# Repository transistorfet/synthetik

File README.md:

Synthetik
=========

###### *Started October 21, 2020*

This project started after I bought some old sound synthesis chips that were commonly used in
video game consoles and computers from the 80s and early 90s.  The first revision is a shield
for an Arduino Mega with 4 different chips: the General Instruments AY-3-8910 / Yamaha YM2149,
the YM2612 / YM3438 (OPN), the YM3812 (OPL2), and the YMF262 (OPL3).  It also has a MIDI in
port, line out stereo jack, and a headphone stereo jack with a TDA1308 power amplifier.

The board design had a large number of issues and mistakes, and I've so far only got it working
with one chip.

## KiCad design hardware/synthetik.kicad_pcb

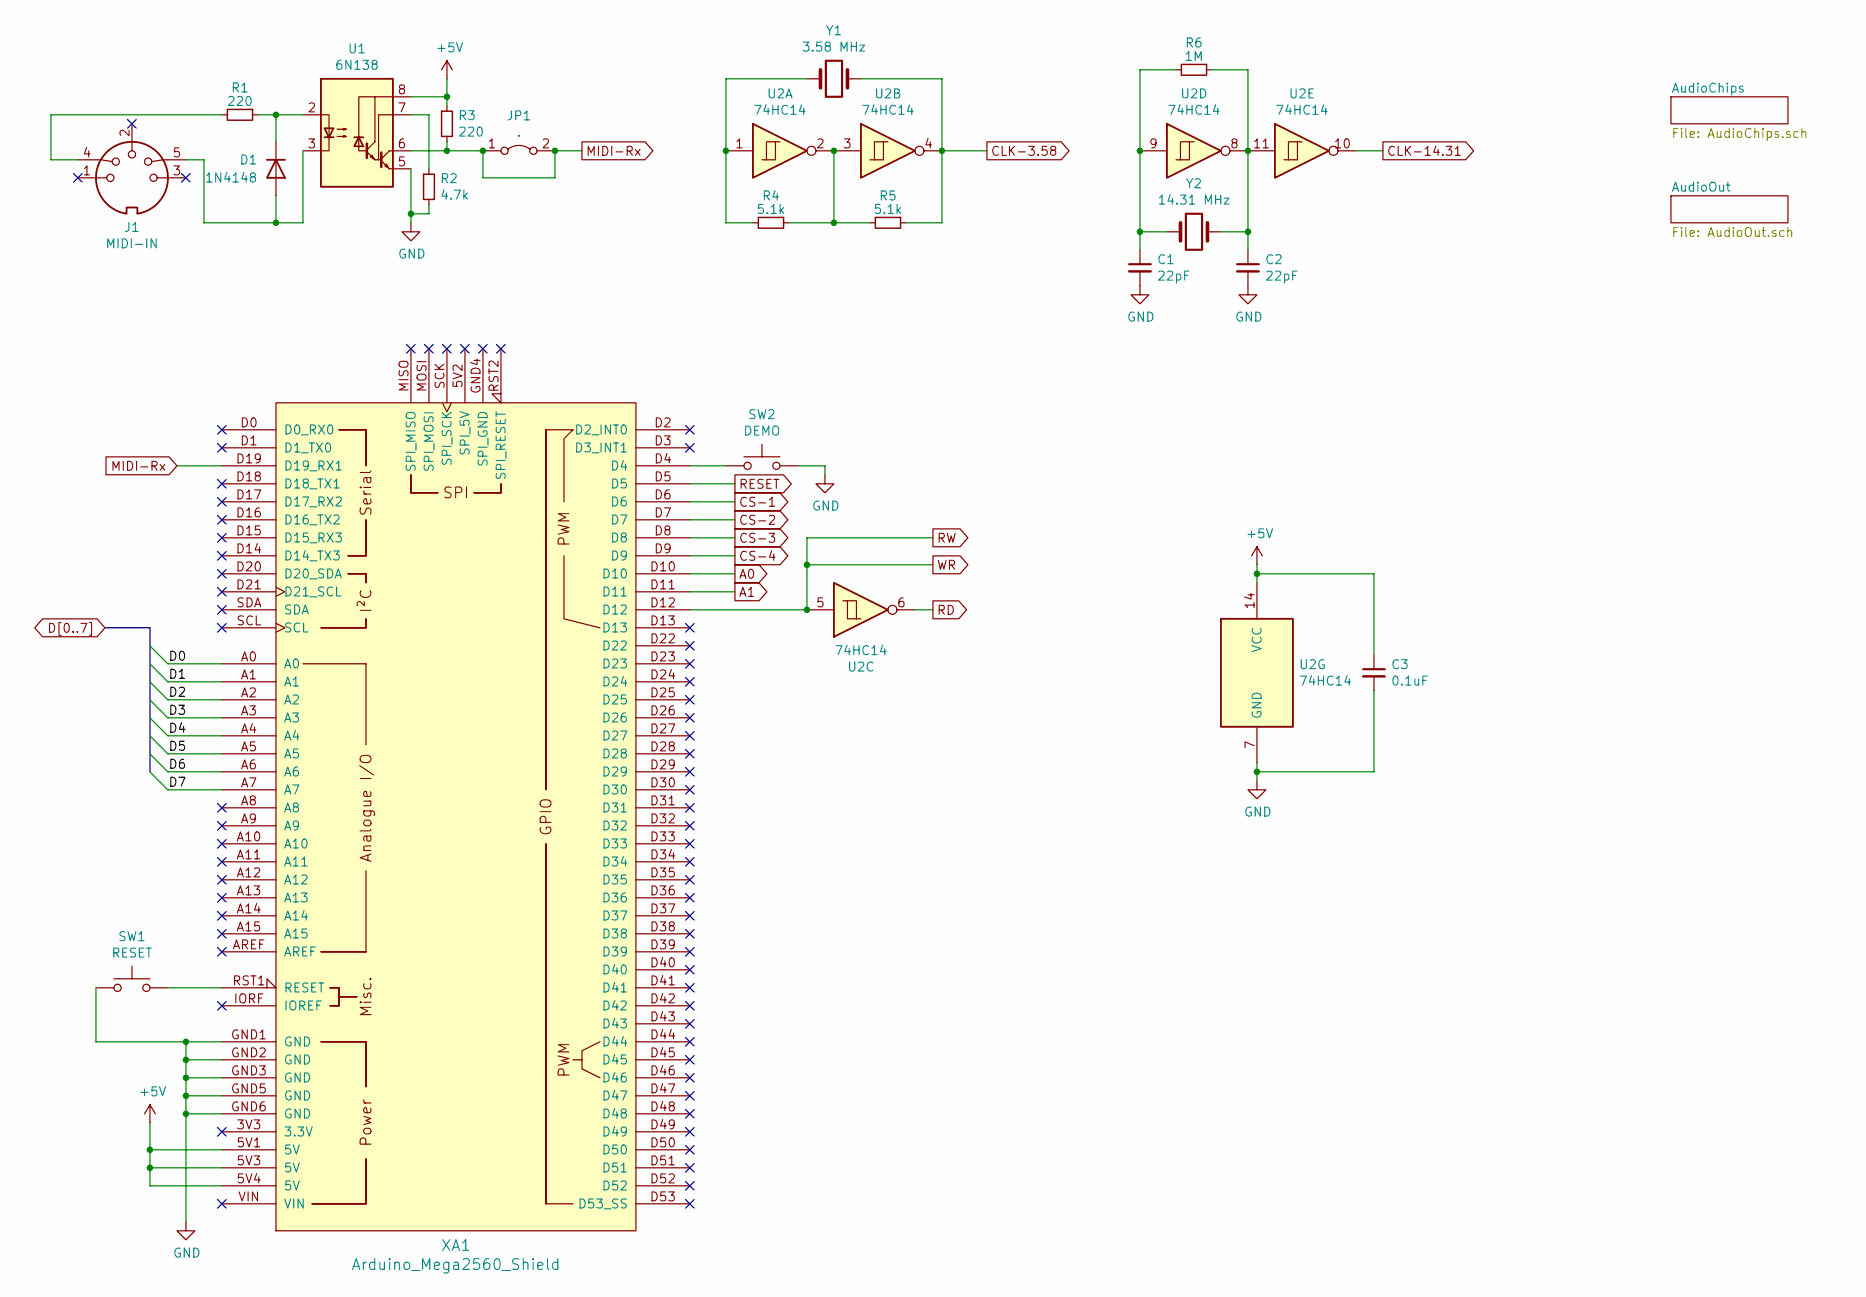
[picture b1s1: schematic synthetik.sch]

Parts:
C1, C2: 22pF; C_Disc_D3.0mm_W2.0mm_P2.50mm
C3: 0.1uF; C_Disc_D3.0mm_W2.0mm_P2.50mm
D1: 1N4148; D_DO-35_SOD27_P7.62mm_Horizontal
J1: MIDI-IN; MIDI_DIN5
JP1: .; PinHeader_1x02_P2.54mm_Vertical
R1, R3: 220; R_Axial_DIN0207_L6.3mm_D2.5mm_P7.62mm_Horizontal
R2: 4.7k; R_Axial_DIN0207_L6.3mm_D2.5mm_P7.62mm_Horizontal
R4, R5: 5.1k; R_Axial_DIN0207_L6.3mm_D2.5mm_P7.62mm_Horizontal
R6: 1M; R_Axial_DIN0207_L6.3mm_D2.5mm_P7.62mm_Horizontal
SW1: RESET; SW_PUSH_6mm
SW2: DEMO; SW_PUSH_6mm
U1: 6N138; DIP-8_W7.62mm_LongPads
U2: 74HC14; DIP-14_W7.62mm_Socket_LongPads
XA1: Arduino_Mega2560_Shield
Y1: 3.58 MHz; Crystal_HC49-4H_Vertical
Y2: 14.31 MHz; Crystal_HC49-4H_Vertical

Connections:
+5V: C3.1, R3.1, U1.8 (VCC), U2.14 (VCC), XA1.5V1 (5V), XA1.5V3 (5V), XA1.5V4 (5V); also elsewhere on the board
A0: XA1.D10; also elsewhere on the board
A1: XA1.D11; also elsewhere on the board
CLK-3.58: R5.1, U2.4, Y1.2; also elsewhere on the board
CLK-14.31: U2.10; also elsewhere on the board
CS-1: XA1.D6; also elsewhere on the board
CS-2: XA1.D7; also elsewhere on the board
CS-3: XA1.D8; also elsewhere on the board
CS-4: XA1.D9; also elsewhere on the board
D0: XA1.A0; also elsewhere on the board
D1: XA1.A1; also elsewhere on the board
D2: XA1.A2; also elsewhere on the board
D3: XA1.A3; also elsewhere on the board
D4: XA1.A4; also elsewhere on the board
D5: XA1.A5; also elsewhere on the board
D6: XA1.A6; also elsewhere on the board
D7: XA1.A7; also elsewhere on the board
GND: C1.2, C2.2, C3.2, R2.2, SW1.1, SW2.2, U1.5 (GND), U2.7 (GND), XA1.GND1 (GND), XA1.GND2 (GND), XA1.GND3 (GND), XA1.GND5 (GND), XA1.GND6 (GND); also elsewhere on the board
MIDI-Rx: JP1.1 (A), JP1.2 (B), R3.2, U1.6 (VO2), XA1.D19 (D19_RX1)
unnamed: C1.1, R6.2, U2.9, Y2.1
unnamed: C2.1, R6.1, U2.8, U2.11, Y2.2
unnamed: D1.1 (K), R1.1, U1.2 (C1)
unnamed: D1.2 (A), J1.5, U1.3 (C2)
unnamed: J1.4, R1.2
unnamed: R2.1, U1.7 (VO1)
unnamed: R4.1, R5.2, U2.2, U2.3
unnamed: R4.2, U2.1, Y1.1
unnamed: SW1.2, XA1.RST1 (RESET)
unnamed: SW2.1, XA1.D4
RD: U2.6; also elsewhere on the board
RESET: XA1.D5; also elsewhere on the board
RW: U2.5, XA1.D12; also elsewhere on the board

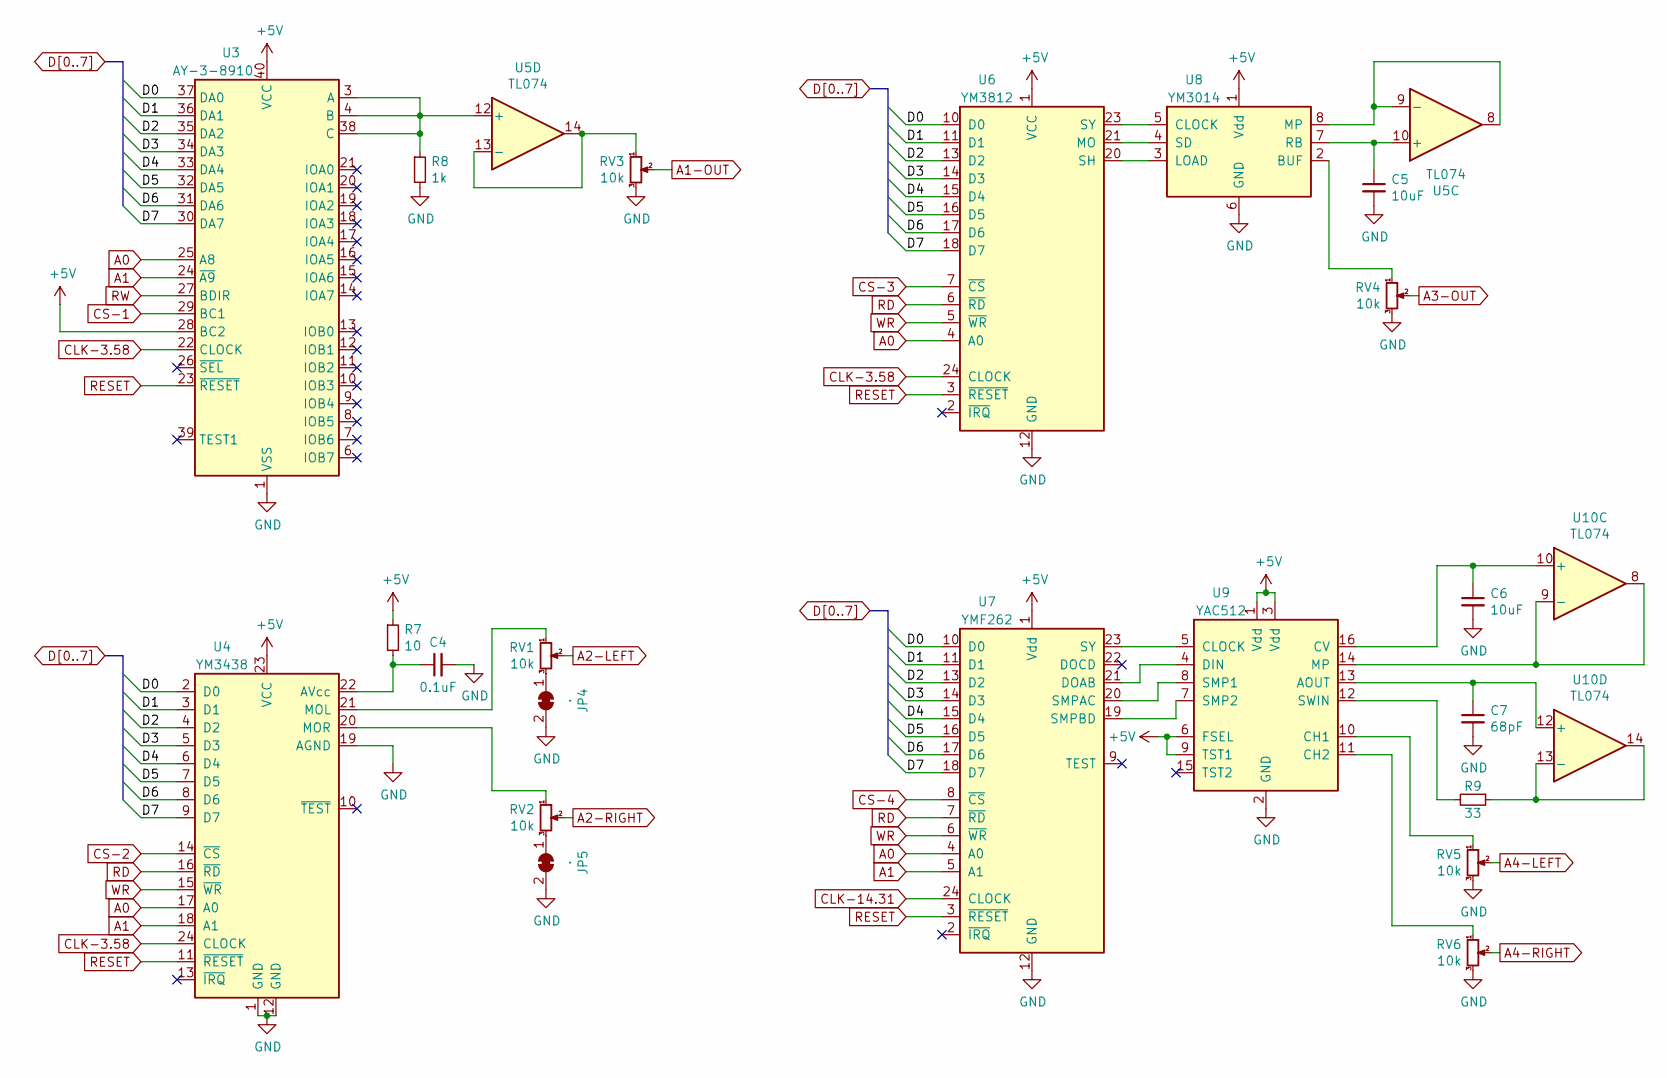
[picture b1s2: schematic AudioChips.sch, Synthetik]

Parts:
C4: 0.1uF; C_Disc_D3.0mm_W2.0mm_P2.50mm
C5, C6: 10uF; CP_Radial_D4.0mm_P1.50mm
C7: 68pF; C_Disc_D3.0mm_W2.0mm_P2.50mm
JP4, JP5: .; SolderJumper-2_P1.3mm_Bridged_RoundedPad1.0x1.5mm
R7: 10; R_Axial_DIN0207_L6.3mm_D2.5mm_P7.62mm_Horizontal
R8: 1k; R_Axial_DIN0207_L6.3mm_D2.5mm_P7.62mm_Horizontal
R9: 33; R_Axial_DIN0207_L6.3mm_D2.5mm_P7.62mm_Horizontal
RV1, RV2, RV3, RV4, RV5, RV6: 10k; Potentiometer_Bourns_3386P_Vertical
U3: AY-3-8910; DIP-40_W15.24mm_Socket_LongPads
U4: YM3438; DIP-24_W15.24mm_Socket_LongPads
U5: TL074; DIP-14_W7.62mm_Socket_LongPads
U6: YM3812; DIP-24_W15.24mm_Socket_LongPads
U7: YMF262; SOP-24_7.5x15.4mm_P1.27mm
U8: YM3014; DIP-8_W7.62mm_Socket_LongPads
U9: YAC512; SOP-16_4.55x10.3mm_P1.27mm
U10: TL074; SOIC-14_3.9x8.7mm_P1.27mm

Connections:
+5V: R7.1, U3.28 (BC2), U3.40 (VCC), U4.23 (VCC), U6.1 (VCC), U7.1 (Vdd), U8.1 (Vdd), U9.1 (Vdd), U9.3 (Vdd), U9.6 (FSEL), U9.9 (TST1); also elsewhere on the board
A0: U3.25 (A8), U4.17 (A0), U6.4 (A0), U7.4 (A0); also elsewhere on the board
A1: U3.24 (~A9), U4.18 (A1), U7.5 (A1); also elsewhere on the board
A1-OUT: RV3.2; also elsewhere on the board
A2-LEFT: RV1.2; also elsewhere on the board
A2-RIGHT: RV2.2; also elsewhere on the board
A3-OUT: RV4.2; also elsewhere on the board
A4-LEFT: RV5.2; also elsewhere on the board
A4-RIGHT: RV6.2; also elsewhere on the board
CLK-3.58: U3.22 (CLOCK), U4.24 (CLOCK), U6.24 (CLOCK); also elsewhere on the board
CLK-14.31: U7.24 (CLOCK); also elsewhere on the board
CS-1: U3.29 (BC1); also elsewhere on the board
CS-2: U4.14 (~CS); also elsewhere on the board
CS-3: U6.7 (~CS); also elsewhere on the board
CS-4: U7.8 (~CS); also elsewhere on the board
D0: U3.37 (DA0), U4.2 (D0), U6.10 (D0), U7.10 (D0); also elsewhere on the board
D1: U3.36 (DA1), U4.3 (D1), U6.11 (D1), U7.11 (D1); also elsewhere on the board
D2: U3.35 (DA2), U4.4 (D2), U6.13 (D2), U7.13 (D2); also elsewhere on the board
D3: U3.34 (DA3), U4.5 (D3), U6.14 (D3), U7.14 (D3); also elsewhere on the board
D4: U3.33 (DA4), U4.6 (D4), U6.15 (D4), U7.15 (D4); also elsewhere on the board
D5: U3.32 (DA5), U4.7 (D5), U6.16 (D5), U7.16 (D5); also elsewhere on the board
D6: U3.31 (DA6), U4.8 (D6), U6.17 (D6), U7.17 (D6); also elsewhere on the board
D7: U3.30 (DA7), U4.9 (D7), U6.18 (D7), U7.18 (D7); also elsewhere on the board
GND: C4.2, C5.2, C6.2, C7.2, JP4.2 (B), JP5.2 (B), R8.2, RV3.3, RV4.3, RV5.3, RV6.3, U3.1 (VSS), U4.1 (GND), U4.12 (GND), U4.19 (AGND), U6.12 (GND), U7.12 (GND), U8.6 (GND), U9.2 (GND); also elsewhere on the board
unnamed: C4.1, R7.2, U4.22 (AVcc)
unnamed: C5.1, U5.10 (+), U8.7 (RB)
unnamed: C6.1, U9.16 (CV), U10.10 (+)
unnamed: C7.1, U9.13 (AOUT), U10.12 (+)
unnamed: JP4.1 (A), RV1.3
unnamed: JP5.1 (A), RV2.3
unnamed: R8.1, U3.3 (A), U3.4 (B), U3.38 (C), U5.12 (+)
unnamed: R9.1, U10.13 (-), U10.14
unnamed: R9.2, U9.12 (SWIN)
unnamed: RV1.1, U4.21 (MOL)
unnamed: RV2.1, U4.20 (MOR)
unnamed: RV3.1, U5.13 (-), U5.14
unnamed: RV4.1, U8.2 (BUF)
unnamed: RV5.1, U9.10 (CH1)
unnamed: RV6.1, U9.11 (CH2)
unnamed: U5.8, U5.9 (-), U8.8 (MP)
unnamed: U6.20 (SH), U8.3 (LOAD)
unnamed: U6.21 (MO), U8.4 (SD)
unnamed: U6.23 (SY), U8.5 (CLOCK)
unnamed: U7.19 (SMPBD), U9.7 (SMP2)
unnamed: U7.20 (SMPAC), U9.8 (SMP1)
unnamed: U7.21 (DOAB), U9.4 (DIN)
unnamed: U7.23 (SY), U9.5 (CLOCK)
unnamed: U9.14 (MP), U10.8, U10.9 (-)
RD: U4.16 (~RD), U6.6 (~RD), U7.7 (~RD); also elsewhere on the board
RESET: U3.23 (~RESET), U4.11 (~RESET), U6.3 (~RESET), U7.3 (~RESET); also elsewhere on the board
RW: U3.27 (BDIR), U4.15 (~WR), U6.5 (~WR), U7.6 (~WR); also elsewhere on the board

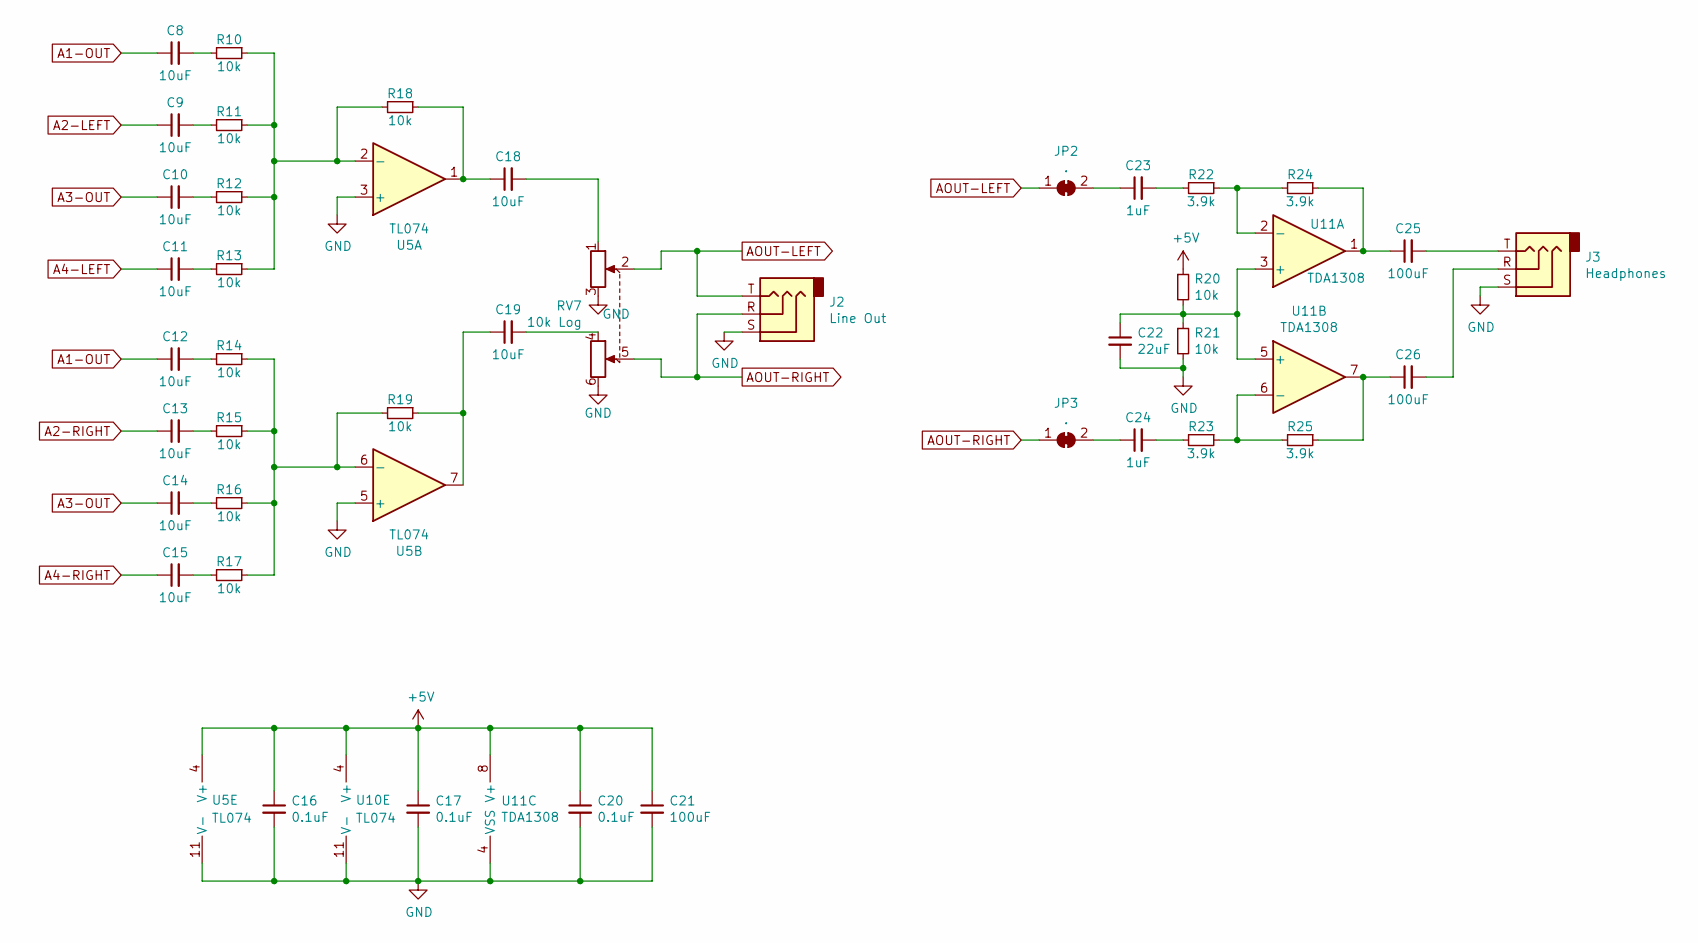
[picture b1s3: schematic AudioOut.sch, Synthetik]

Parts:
C8, C9, C10, C11, C12, C13, C14, C15, C18, C19: 10uF; CP_Radial_D4.0mm_P1.50mm
C16, C17, C20: 0.1uF; C_Disc_D3.0mm_W2.0mm_P2.50mm
C21, C25, C26: 100uF; CP_Radial_D6.3mm_P2.50mm
C22: 22uF; CP_Radial_D6.3mm_P2.50mm
C23, C24: 1uF; C_Disc_D3.0mm_W2.0mm_P2.50mm
J2: Line Out; Jack_3.5mm_CUI_SJ1-3533NG_Horizontal
J3: Headphones; Jack_3.5mm_CUI_SJ1-3533NG_Horizontal
JP2, JP3: .; SolderJumper-2_P1.3mm_Bridged_RoundedPad1.0x1.5mm
R10, R11, R12, R13, R14, R15, R16, R17, R18, R19, R20, R21: 10k; R_Axial_DIN0207_L6.3mm_D2.5mm_P7.62mm_Horizontal
R22, R23, R24, R25: 3.9k; R_Axial_DIN0207_L6.3mm_D2.5mm_P7.62mm_Horizontal
RV7: 10k Log; Potentiometer_Alpha_RD902F-40-00D_Dual_Vertical
U5: TL074; DIP-14_W7.62mm_Socket_LongPads
U10: TL074; SOIC-14_3.9x8.7mm_P1.27mm
U11: TDA1308; DIP-8_W7.62mm_Socket_LongPads

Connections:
+5V: C16.1, C17.1, C20.1, C21.1, R20.1, U5.4 (V+), U10.4 (V+), U11.8 (V+); also elsewhere on the board
A1-OUT: C8.1, C12.1; also elsewhere on the board
A2-LEFT: C9.1; also elsewhere on the board
A2-RIGHT: C13.1; also elsewhere on the board
A3-OUT: C10.1, C14.1; also elsewhere on the board
A4-LEFT: C11.1; also elsewhere on the board
A4-RIGHT: C15.1; also elsewhere on the board
AOUT-LEFT: J2.T, JP2.1 (A), RV7.2
AOUT-RIGHT: J2.R, JP3.1 (A), RV7.5
GND: C16.2, C17.2, C20.2, C21.2, C22.2, J2.S, J3.S, R21.2, RV7.3, RV7.6, U5.3 (+), U5.5 (+), U5.11 (V-), U10.11 (V-), U11.4 (VSS); also elsewhere on the board
unnamed: C8.2, R10.2
unnamed: C9.2, R11.2
unnamed: C10.2, R12.2
unnamed: C11.2, R13.2
unnamed: C12.2, R14.2
unnamed: C13.2, R15.2
unnamed: C14.2, R16.2
unnamed: C15.2, R17.2
unnamed: C18.1, R18.1, U5.1
unnamed: C18.2, RV7.1
unnamed: C19.1, R19.1, U5.7
unnamed: C19.2, RV7.4
unnamed: C22.1, R20.2, R21.1, U11.3 (+), U11.5 (+)
unnamed: C23.1, JP2.2 (B)
unnamed: C23.2, R22.2
unnamed: C24.1, JP3.2 (B)
unnamed: C24.2, R23.2
unnamed: C25.1, R24.1, U11.1
unnamed: C25.2, J3.T
unnamed: C26.1, R25.1, U11.7
unnamed: C26.2, J3.R
unnamed: R10.1, R11.1, R12.1, R13.1, R18.2, U5.2 (-)
unnamed: R14.1, R15.1, R16.1, R17.1, R19.2, U5.6 (-)
unnamed: R22.1, R24.2, U11.2 (-)
unnamed: R23.1, R25.2, U11.6 (-)

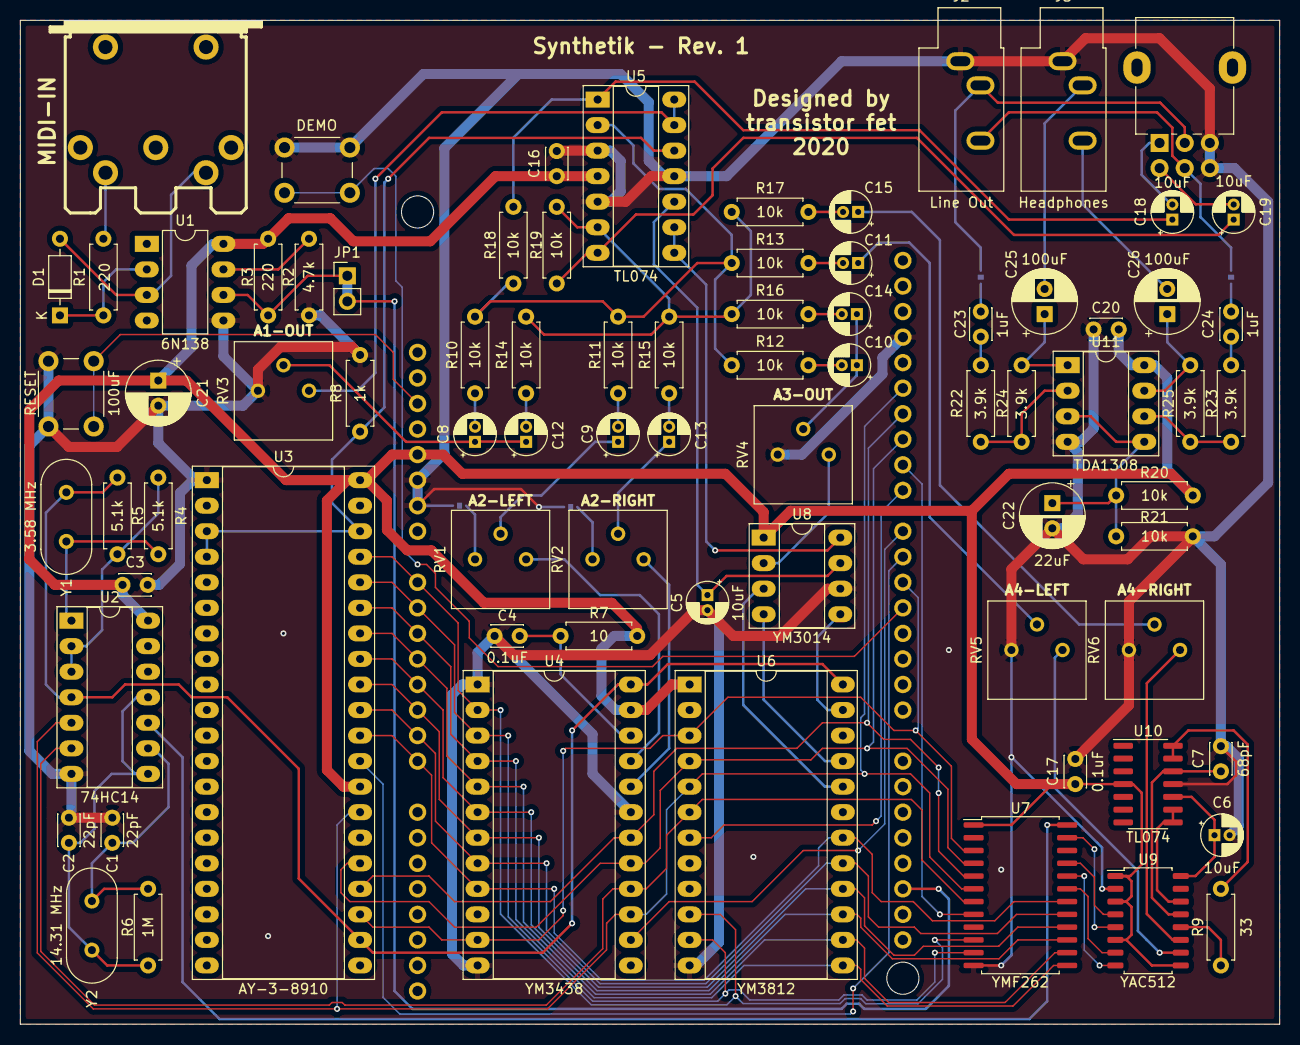
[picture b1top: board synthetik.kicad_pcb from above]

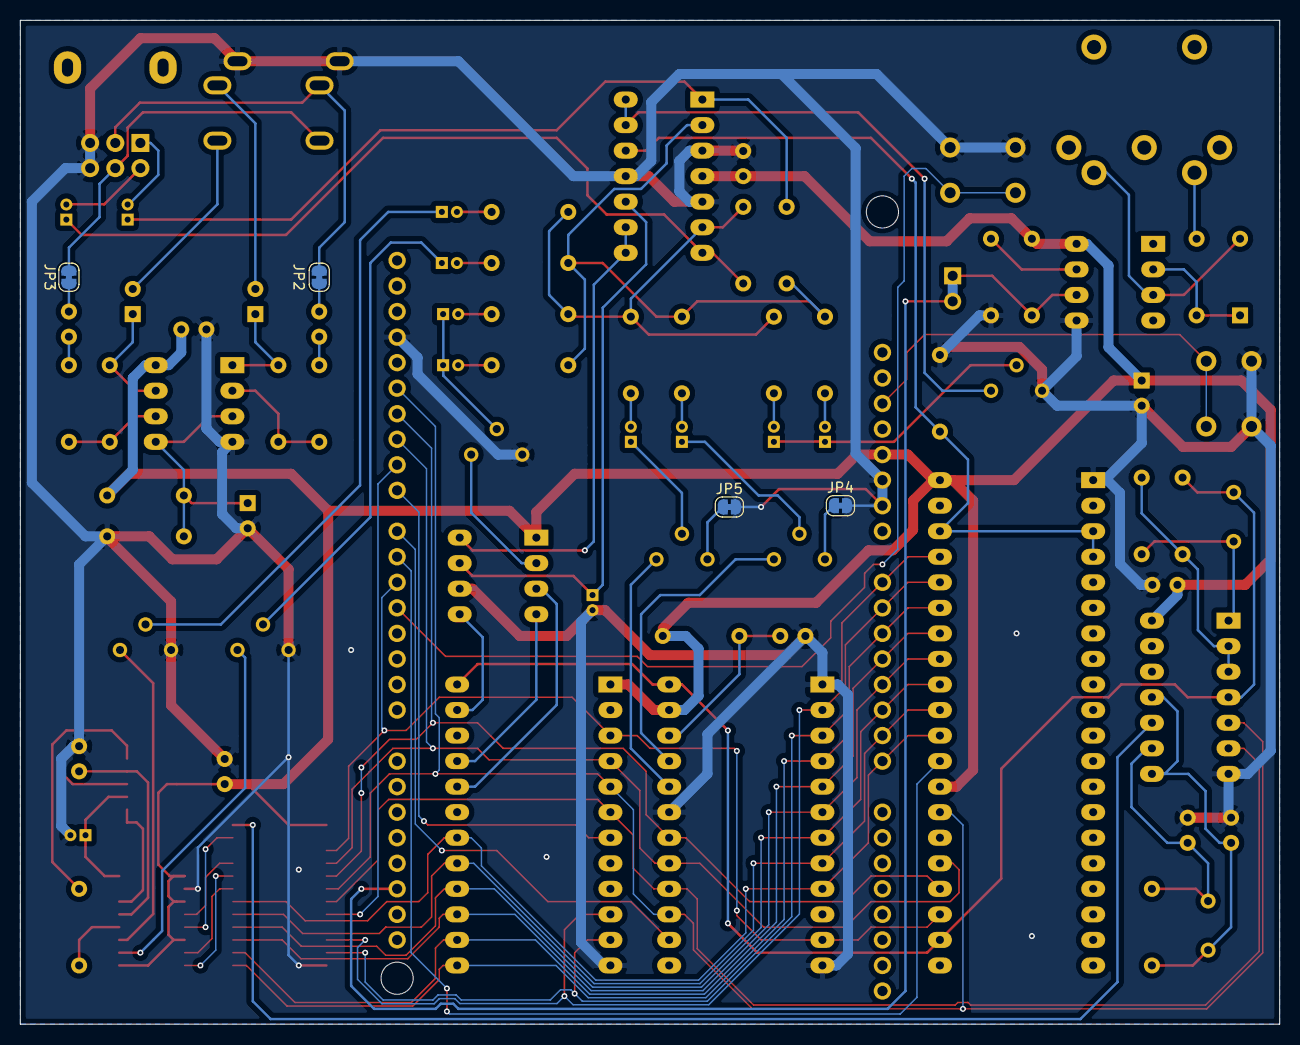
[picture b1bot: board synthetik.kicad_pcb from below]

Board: 2 copper layers, 125.2 x 99.8 mm, 83 parts (4 on the bottom side), 89 nets.

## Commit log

2020-10-22 Initialized repository with work in progress
2020-11-10 Added instruments and midi interface
2020-11-24 Various updates and playing with breadboarded chips
2020-11-24 Added PCB design
2020-12-05 Final rev.1 PCB design
2020-12-05 Added readme
2021-03-09 Updated with YM2612/YM3438 controls
2021-09-04 Playing around with YM3812 instruments
